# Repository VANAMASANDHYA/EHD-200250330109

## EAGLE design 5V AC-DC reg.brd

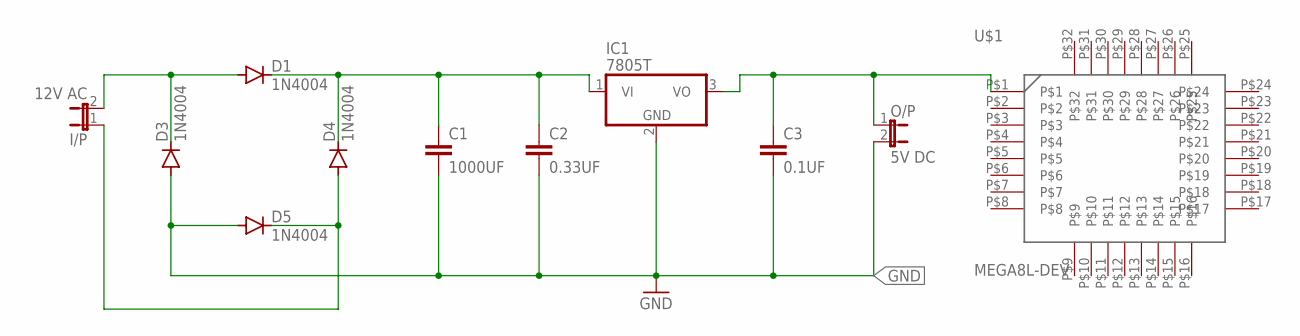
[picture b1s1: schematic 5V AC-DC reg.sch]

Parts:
C1: 1000UF; C2.5-3
C2: 0.33UF; C2.5-3
C3: 0.1UF; C2.5-3
D1, D3, D4, D5: 1N4004; DO41-10
I/P: 12V AC; JP1
IC1: 7805T; TO220H
O/P: 5V DC; JP1
U$1: MEGA8L-DEV; TQFP-MEGA8L

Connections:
GND: C1.2, C2.2, C3.2, D3.A, D5.A, IC1.2 (GND), O/P.2
unnamed: D1.A, D3.C, I/P.2
unnamed: C1.1, C2.1, D1.C, D4.C, IC1.1 (VI)
unnamed: D4.A, D5.C, I/P.1
unnamed: C3.1, IC1.3 (VO), O/P.1, U$1.P$1

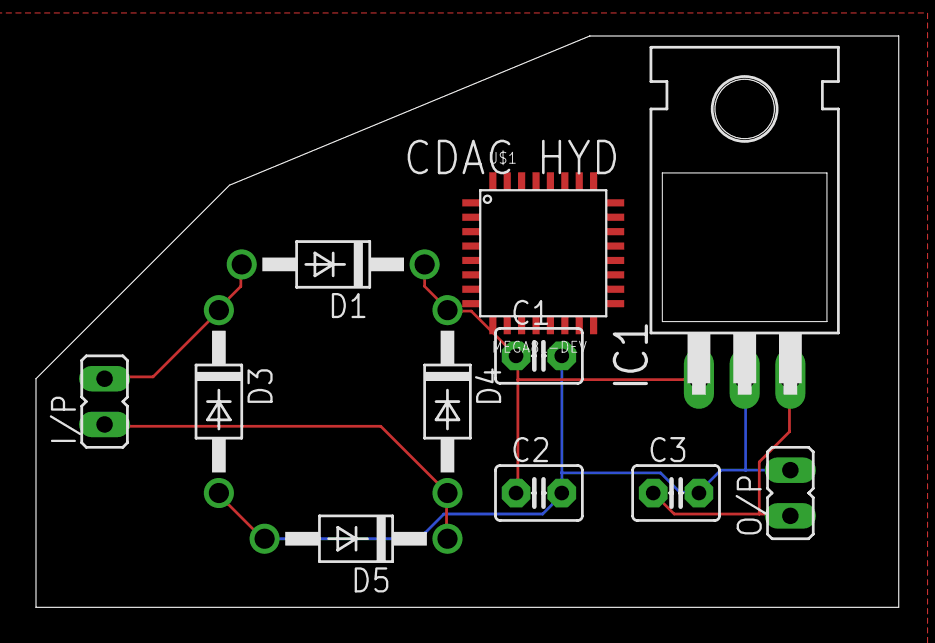
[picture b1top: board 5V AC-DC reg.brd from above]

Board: 2 copper layers, 47.9 x 31.7 mm, 11 parts (0 on the bottom side), 5 nets.
